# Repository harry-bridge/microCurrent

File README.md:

## Micro Current

A clone of Dave Jone's µCurrent board using parts that can be easily purchased in the UK (mostly)

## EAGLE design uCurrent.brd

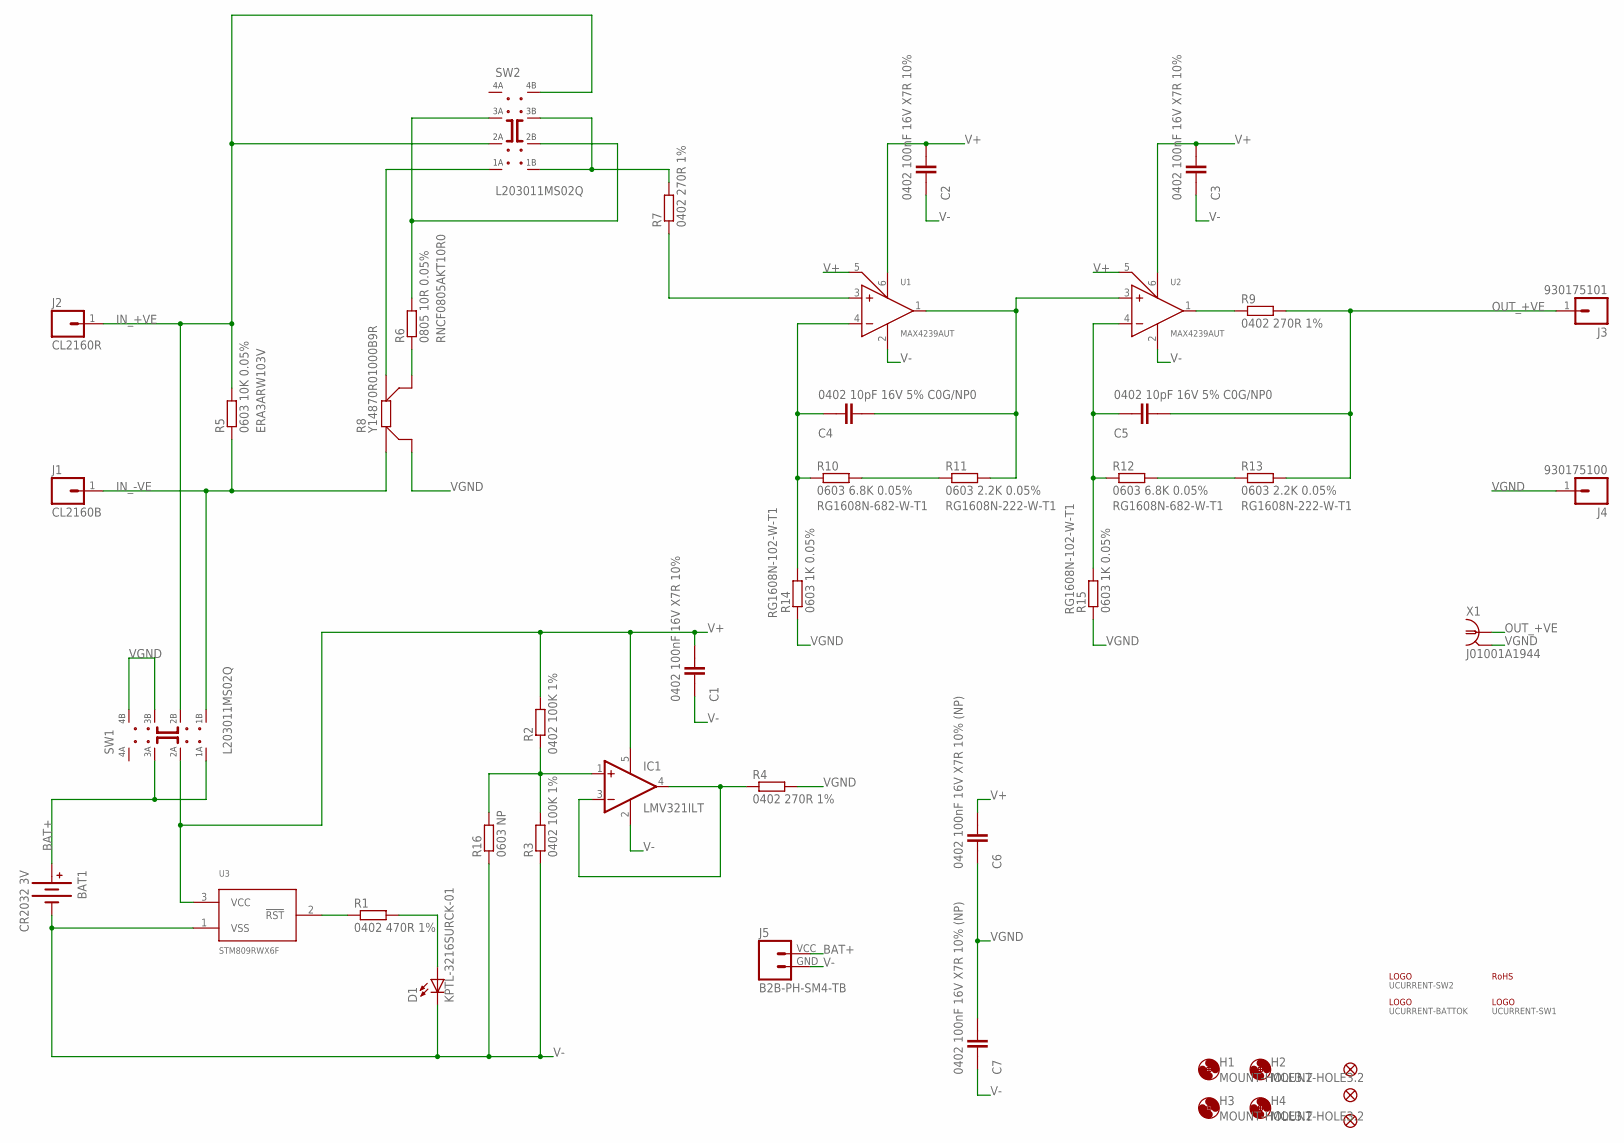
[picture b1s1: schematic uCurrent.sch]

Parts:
BAT1: CR2032 3V; KEYSTONE_1058
C1, C2, C3: 0402 100nF 16V X7R 10%; C0402-SMALLER
C4, C5: 0402 10pF 16V 5% C0G/NP0; C0402-SMALLER
C6, C7: 0402 100nF 16V X7R 10% (NP); C0402-SMALLER
D1: KPTL-3216SURCK-01; KPTL-3216
H1, H2, H3, H4: MOUNT-HOLE3.2; 3,2
IC1: LMV321ILT; SOT23-5
J1: CL2160B; CL2160R
J2: CL2160R
J3: 930175101; BUG10_SOCKET
J4: 930175100; BUG10_SOCKET
J5: B2B-PH-SM4-TB; JST-PH-SMD-VERT-02
JP1, JP2, JP3: FIDUCIAL1X2.5-STOP; FIDUCIAL-1X2.5-STOP
L1: UCURRENT-BATTOK; UCURRENT_BATTOK
L2: UCURRENT-SW1; UCURRENT_SW1
L3: UCURRENT-SW2; UCURRENT_SW2
R1: 0402 470R 1%; R0402-SMALLER
R2, R3: 0402 100K 1%; R0402-SMALLER
R4, R7, R9: 0402 270R 1%; R0402-SMALLER
R5: 0603 10K 0.05%; C0603K-SMALL; MPN ERA3ARW103V
R6: 0805 10R 0.05%; R0805; MPN RNCF0805AKT10R0
R8: Y14870R01000B9R; CSM2512-L
R10, R12: 0603 6.8K 0.05%; C0603K-SMALL; MPN RG1608N-682-W-T1
R11, R13: 0603 2.2K 0.05%; C0603K-SMALL; MPN RG1608N-222-W-T1
R14, R15: 0603 1K 0.05%; C0603K-SMALL; MPN RG1608N-102-W-T1
R16: 0603 NP; C0603K-SMALL
SW1, SW2: L203011MS02Q
U1, U2: MAX4239AUT; SOT-23-6
U3: STM809RWX6F; SOT23-3
U$1: ROHS-1MM
X1: J01001A1944

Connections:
BAT+: BAT1.+VE (+), J5.VCC (2), SW1.1, SW1.3
IN_+VE: J2.1, R5.2, SW1.6, SW2.2, SW2.8
IN_-VE: J1.1, R5.1, R8.I1 (A), SW1.5
unnamed: R1.1, U3.2 (!RST)
unnamed: IC1.1 (+IN), R2.1, R3.2, R16.2
unnamed: IC1.3 (-IN), IC1.4 (OUT), R4.1
unnamed: R7.2, SW2.5, SW2.7
unnamed: R6.1, R8.E2 (C)
unnamed: R8.I2 (D), SW2.1
unnamed: R6.2, SW2.3, SW2.6
unnamed: R7.1, U1.3
unnamed: C4.1, R11.2, U1.1, U2.3
unnamed: C4.2, R10.1, R14.2, U1.4
unnamed: R10.2, R11.1
unnamed: C5.2, R12.1, R15.2, U2.4
unnamed: R12.2, R13.1
unnamed: D1.A, R1.2
unnamed: R9.1, U2.1
OUT_+VE: C5.1, J3.1, R9.2, R13.2, X1.1
V+: C1.1, C2.1, C3.1, C6.1, IC1.5 (V+), R2.2, SW1.2, U1.5, U1.6, U2.5, U2.6, U3.3 (VCC)
V-: BAT1.-VE (-), C1.2, C2.2, C3.2, C7.2, D1.C, IC1.2 (V-), J5.GND (1), R3.1, R16.1, U1.2, U2.2, U3.1 (VSS)
VGND: C6.2, C7.1, J4.1, R4.2, R8.E1 (B), R14.1, R15.1, SW1.7, SW1.8, X1.2, X1.3 (2), X1.4 (2), X1.5 (2)

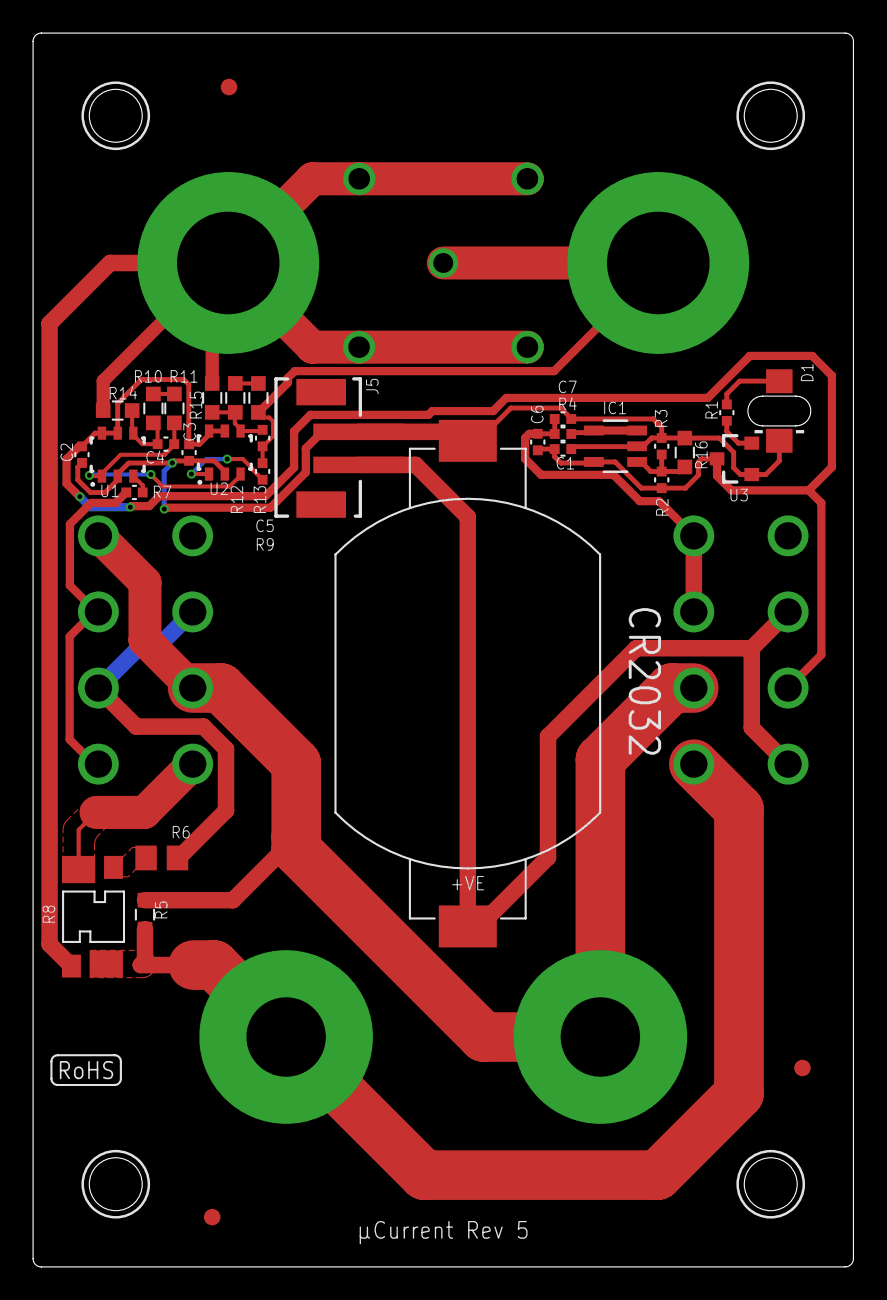
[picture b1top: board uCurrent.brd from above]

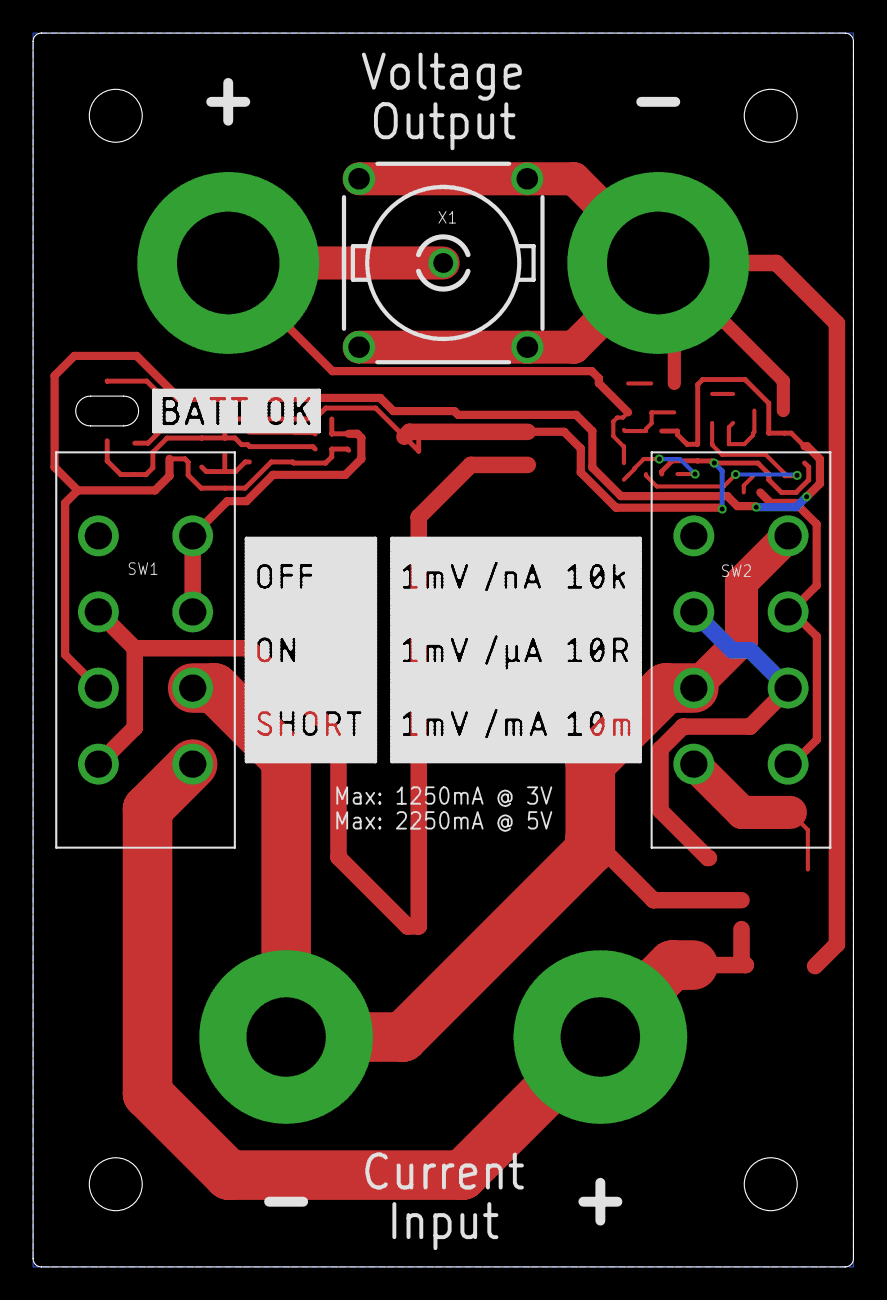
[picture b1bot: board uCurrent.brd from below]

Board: 2 copper layers, 49.6 x 74.6 mm, 48 parts (10 on the bottom side), 22 nets.

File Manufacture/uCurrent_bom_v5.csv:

"Qty","Value","Device","Parts",
"2","0402 10pF 16V 5% C0G/NP0","C-EUC0402-SMALLER","C4, C5",
"2","0402 100K 1%","R-EU_R0402-SMALLER","R2, R3",
"3","0402 100nF 16V X7R 10%","C-EUC0402-SMALLER","C1, C2, C3",
"2","0402 100nF 16V X7R 10% (NP)","C-EUC0402-SMALLER","C6, C7",
"3","0402 270R 1%","R-EU_R0402-SMALLER","R4, R7, R9",
"1","0402 470R 1%","R-EU_R0402-SMALLER","R1",
"2","0603 1K 0.05%","R-EU_0603K-SMALL","R14, R15",
"2","0603 2.2K 0.05%","R-EU_0603K-SMALL","R11, R13",
"2","0603 6.8K 0.05%","R-EU_0603K-SMALL","R10, R12",
"1","0603 10K 0.05%","R-EU_0603K-SMALL","R5",
"1","0603 NP","R-EU_0603K-SMALL","R16",
"1","0805 10R 0.05%","R-EU_R0805","R6",
"1","930175100","M01-BUG10","J4",
"1","930175101","M01-BUG10","J3",
"1","B2B-PH-SM4-TB","M02-JST-PH-SMD-VERT","J5",
"2","CL2160R","M01-CL2160R","J1, J2",
"1","CR2032 3V","BATTERY-KEYSTONE_1058","BAT1",
"3","FIDUCIAL1X2.5-STOP","FIDUCIAL1X2.5-STOP","JP1, JP2, JP3",
"1","J01001A1944","BNC_J01001A1944","X1",
"1","KPTL-3216SURCK-01","LED-KPTL-3216","D1",
"2","L203011MS02Q","SWITCH-DP3T-L203011MS02Q","SW1, SW2",
"1","LMV321ILT","LMV321M5X","IC1",
"2","MAX4239AUT","MAX4239","U1, U2",
"4","MOUNT-HOLE3.2","MOUNT-HOLE3.2","H1, H2, H3, H4",
"1","ROHS-1MM","ROHS-1MM","U$1",
"1","STM809RWX6F","STM809RWX6F","U3",
"1","UCURRENT-BATTOK","UCURRENT-BATTOK","L1",
"1","UCURRENT-SW1","UCURRENT-SW1","L2",
"1","UCURRENT-SW2","UCURRENT-SW2","L3",
"1","Y14870R01000B9R","R-EU_KELVIN_Y14870R01000B9R","R8",

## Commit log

2020-02-01 Initial Commit of board files
2020-02-01 Gerbers
2020-02-01 Add board images
2020-02-03 Small updates and gerbers
2020-02-19 Small tweaks
